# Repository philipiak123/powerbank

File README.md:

# 1S Li-Ion Powerbank with TP4056 Charger and BMS

## Overview

This project is a single-cell (1S) lithium-ion powerbank designed for 3.7V Li-Ion batteries (4.2V fully charged).

The board integrates:

* Li-Ion linear charging circuit (TP4056)
* Battery Management System (BMS) for protection
* PCB designed in KiCad
* Local symbol and footprint libraries included in repository

The design is intended for educational use, prototyping, and small-scale DIY applications.

---

## System Architecture

The powerbank consists of:

1. Li-Ion Cell (1S, 3.7V nominal)
2. TP4056 charging IC (CC/CV charger)
3. Protection circuit (BMS)
4. Output stage (battery output terminals / USB if implemented)

---

## Battery Specification

* Battery type: Lithium-Ion (Li-Ion)
* Configuration: 1S (single cell)
* Nominal voltage: 3.7V
* Fully charged voltage: 4.2V
* Recommended cell type: 18650
* Recommended capacity: 2000–3500mAh

⚠ Only use high-quality and undamaged cells.

---

## Charging Circuit – TP4056

The design uses the TP4056 linear Li-Ion charger IC.

Charging method:

* CC/CV (Constant Current / Constant Voltage)
* Charge termination voltage: 4.2V ±1%
* Programmable charge current via RPROG resistor
* Typical charge current: up to 1A (depends on RPROG value)
* Input voltage: 5V (USB supply)

Important notes:

* The TP4056 is a linear charger and dissipates power as heat.
* Provide sufficient copper area under the IC for thermal dissipation.
* High charge current increases temperature significantly.

Charge status pins:

* CHRG – charging indicator
* STDBY – charge complete indicator

---

## BMS Protection Features

The Battery Management System provides:

* Overcharge protection
* Overdischarge protection
* Overcurrent protection
* Short-circuit protection

Typical protection thresholds (may vary depending on protection IC used):

* Overcharge cutoff: ~4.25V
* Overdischarge cutoff: ~2.5–2.7V
* Overcurrent threshold: depends on MOSFET and design

---

## Electrical Parameters

* Battery configuration: 1S
* Maximum charge current: up to 1A (configurable)
* Maximum discharge current: depends on MOSFET and PCB trace width
* Input voltage: 5V
* Output voltage: 3.0–4.2V (battery dependent)

---

## PCB Information

* 2-layer PCB
* Designed in KiCad
* Custom symbol and footprint libraries included in repository
* Gerber files available for manufacturing

PCB files:

* powerbank.kicad_sch – schematic
* powerbank.kicad_pcb – PCB layout
* Gerbers located in `/hardware/gerbers`

---

## Repository Structure

```
/hardware
 ├── pcb
 ├── libraries
 │    ├── symbols
 │    └── footprints
 ├── gerbers
 └── bom
```

Local libraries are included to ensure portability of the project.

---

## Manufacturing

To manufacture the board:

1. Use Gerber files from `/hardware/gerbers`
2. Upload them to your PCB manufacturer
3. Verify drill and copper layers before ordering

Recommended:

* 1oz copper
* FR4 substrate
* 2-layer board

---

## Safety Notice

Lithium-ion batteries can be dangerous if misused.

* Do not short-circuit the battery
* Do not overcharge or overdischarge
* Do not use damaged or swollen cells
* Do not leave charging unattended
* Do not exceed recommended charge current

Use this project at your own risk.

---

## Disclaimer

This project is provided for educational purposes only.
The author assumes no responsibility for damage, injury, or loss resulting from improper use.

---

## License

Open-source hardware project.
You may modify and use it for personal, educational, and non-commercial purposes.

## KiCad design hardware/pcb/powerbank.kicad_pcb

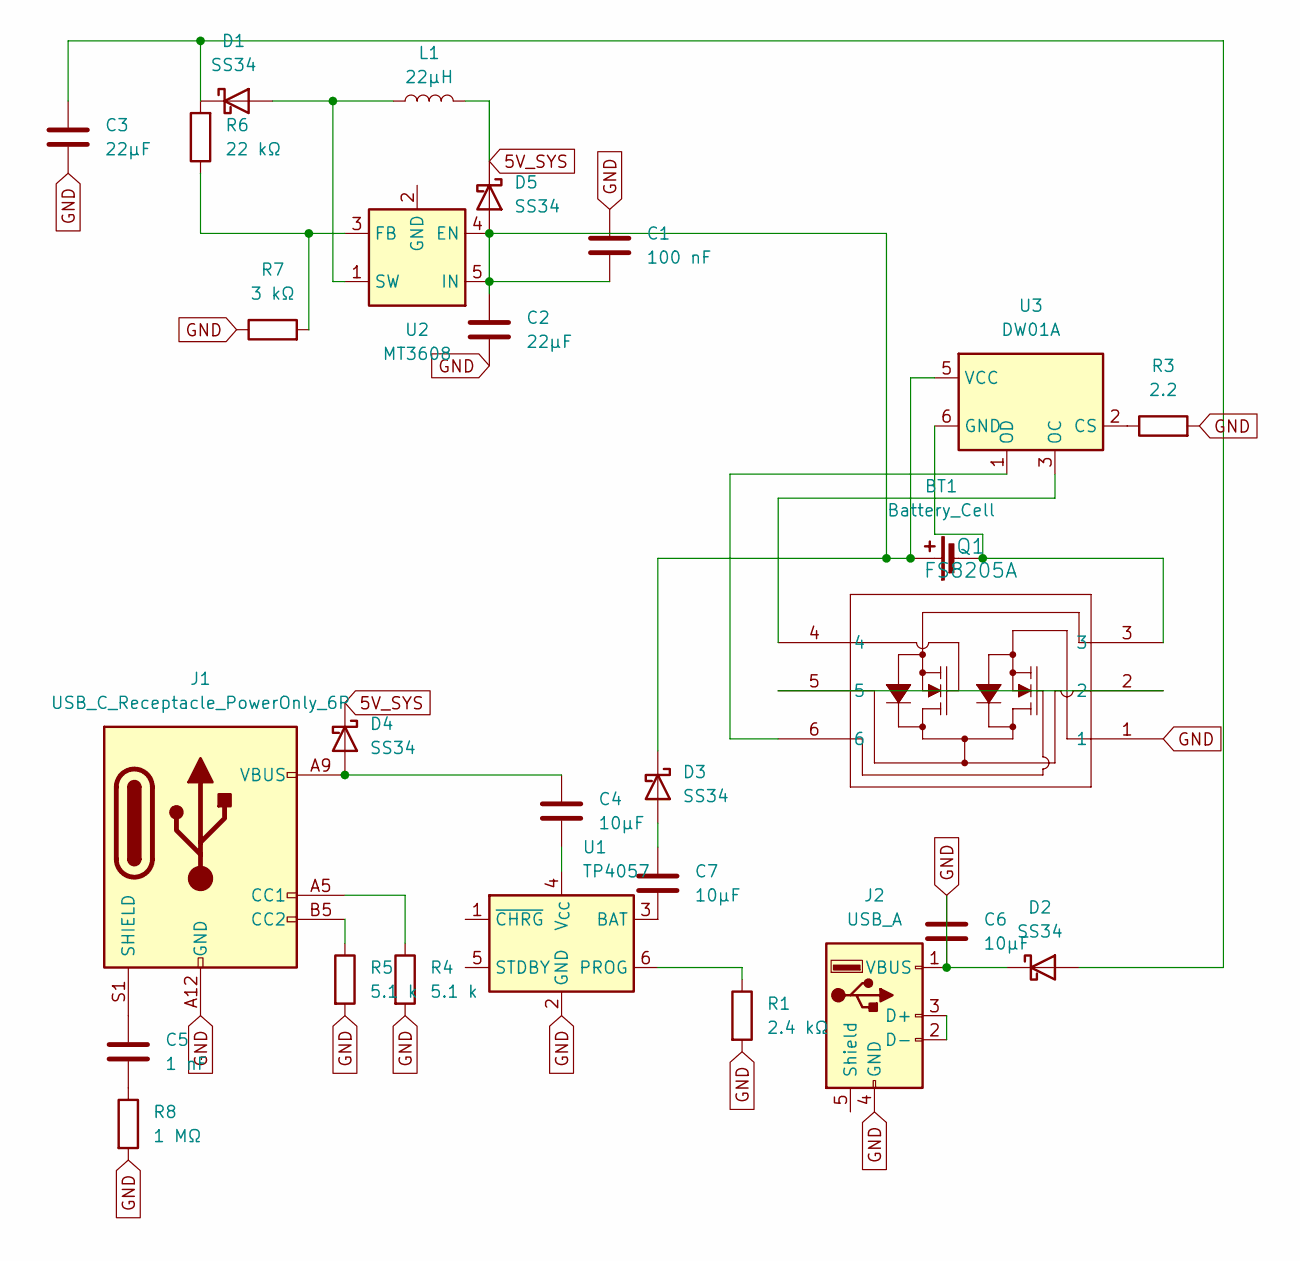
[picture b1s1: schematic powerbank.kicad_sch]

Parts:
BT1: Battery_Cell; Bez_nazwy_1
C1: 100 nF; C_0805_2012Metric
C2, C3: 22μF; C_0805_2012Metric
C4, C6, C7: 10μF; C_0805_2012Metric
C5: 1 nF; C_0805_2012Metric
D1, D2, D3, D4, D5: SS34; D_SMA
J1: USB_C_Receptacle_PowerOnly_6P; USB_C_Receptacle_HRO_TYPE-C-31-M-12
J2: USB_A; USB_A_Molex_67643_Horizontal
L1: 22μH; L_7.3x7.3_H4.5
Q1: FS8205A; SOT-23-6L_TCP
R1: 2.4 kΩ; R_0805_2012Metric
R3: 2.2; R_0805_2012Metric
R4, R5: 5.1 k; R_0805_2012Metric
R6: 22 kΩ; R_0805_2012Metric
R7: 3 kΩ; R_0805_2012Metric
R8: 1 MΩ; R_0805_2012Metric
U1: TP4057; TSOT-23-6
U2: MT3608; SOT-23-6
U3: DW01A; SOT-23-6

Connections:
5V_SYS: D4.1 (K), D5.1 (K), L1.2
GND: C1.1, C2.2, C3.2, C6.1, C6.2, D2.1 (K), J1.A1, J1.A12 (GND), J1.B1, J1.B12 (GND), J2.1 (VBUS), J2.4 (GND), Q1.1, R1.2, R3.2, R4.2, R5.2, R7.1, R8.2, U1.2 (GND)
unnamed: BT1.1 (+), C1.2, C2.1, D3.1 (K), D5.2 (A), U2.4 (EN), U2.5 (IN), U3.5 (VCC)
unnamed: BT1.2 (-), Q1.3, U3.6 (GND)
unnamed: C5.2, R8.1
unnamed: D1.2 (A), L1.1, U2.1 (SW)
unnamed: C3.1, D1.1 (K), D2.2 (A), R6.2
unnamed: C7.1, D3.2 (A)
unnamed: C4.1, D4.2 (A), J1.A4, J1.A9 (VBUS), J1.B4, J1.B9 (VBUS)
unnamed: J1.A5 (CC1), R4.1
unnamed: J1.B5 (CC2), R5.1
unnamed: C5.1, J1.S1 (SHIELD)
unnamed: J2.2 (D-), J2.3 (D+)
unnamed: Q1.2, Q1.5
unnamed: C7.2, U1.3 (BAT)
unnamed: R1.1, U1.6 (PROG)
unnamed: C4.2, U1.4 (V_{CC})
unnamed: R6.1, R7.2, U2.3 (FB)
unnamed: R3.1, U3.2 (CS)
unnamed: Q1.4, U3.3 (OC)
unnamed: Q1.6, U3.1 (OD)

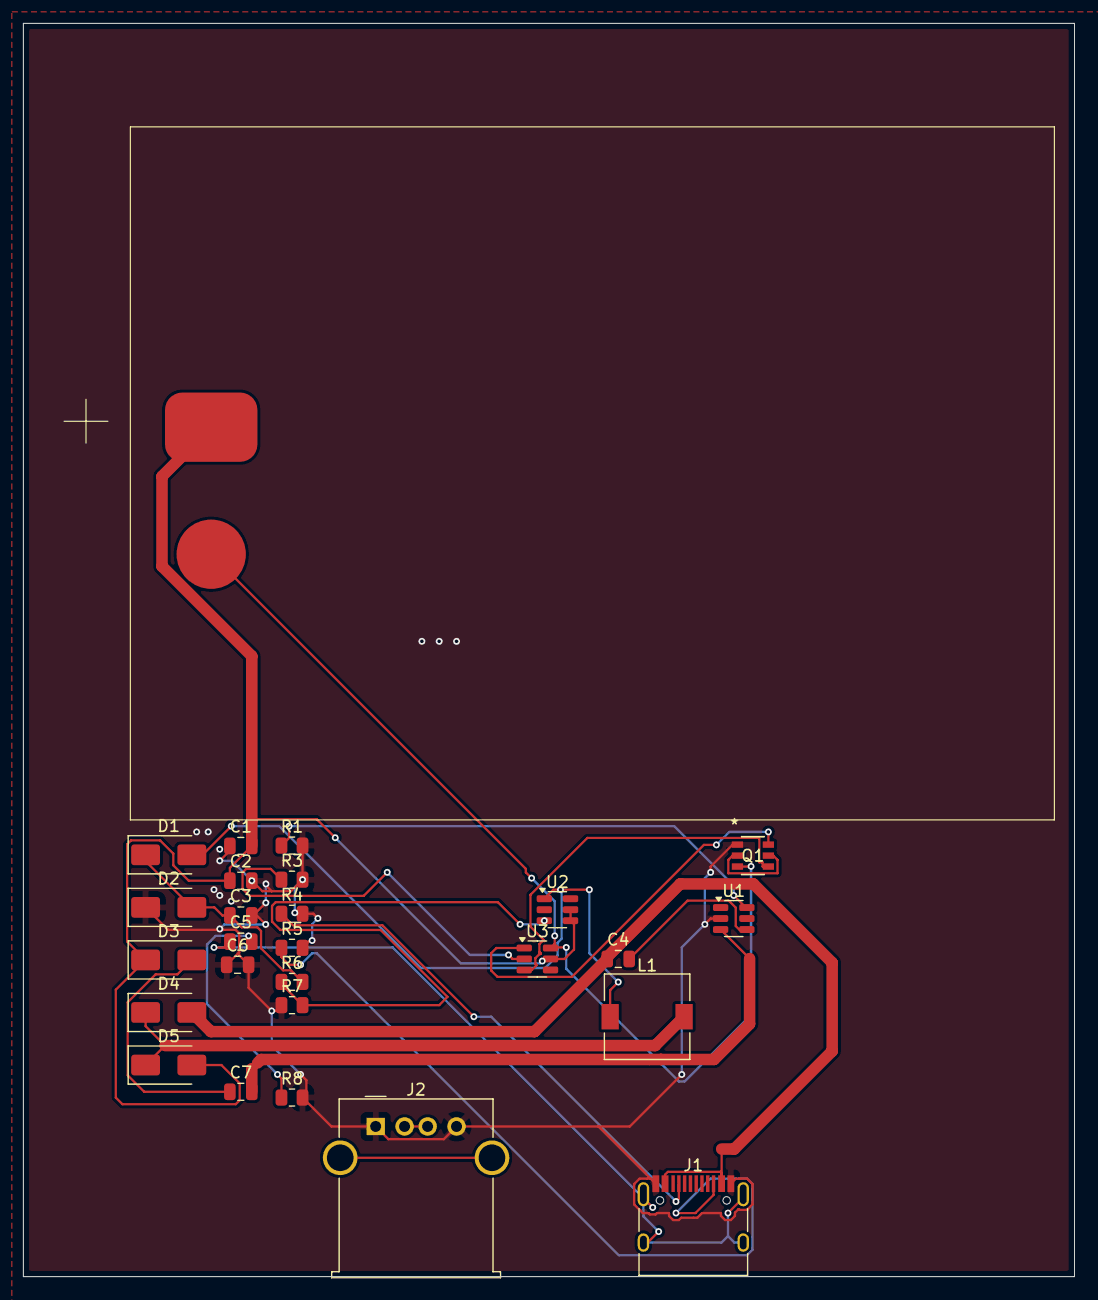
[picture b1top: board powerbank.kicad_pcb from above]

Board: 2 copper layers, 91.0 x 108.5 mm, 27 parts (0 on the bottom side), 21 nets.

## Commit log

2026-03-04 Create libraries
